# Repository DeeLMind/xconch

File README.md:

# 神奇海螺

***

## 简介

是时候该结束开发板裸奔的时代了。采用堆叠设计，拥有漂亮外观及超强扩展性。一款完全开源的结构及通用硬件扩展平台，旨在大家能更欢乐的DIY。

项目首页：https://github.com/xboot/xconch

## 名称的由来

神奇海螺，源自网友`word天`lymz@foxmail.com(QQ928882442)的网名，只因在激烈的项目取名讨论中，一张惊天图片，高逼格的意境，贴合式奶骑，迅速定论，结束了`一个完全开源的，未知项目名称的，有着炫酷外观及超强堆叠扩展性的装逼DIY套件`混沌态描述。

在这里同样感谢如下网友参与头脑风暴，积极献计献策。排名不分先后，如有遗漏还请海涵：

| 网名         | QQ         |
| ---------- | ---------- |
| 非飞         | 6278495    |
| 挖坑侠晕哥      | 516333132  |
| 迪卡魏曼依奇君    | 932668000  |
| Val劲       | 2452013147 |
| Bumbee     | 1059270763 |
| 忽忽         | 12931577   |
| Dictionary | 179670618  |
| 怪盗Kid      | 783837037  |
| 暗╰☆╮夜      | 2819617028 |
| 已完成。 成。 成。 | 2495841298 |
| flame      | 470230832  |
| Robe       | 82796620   |
| 橘子         | 2535418266 |
| 肠子         | 553010120  |
| 〃阿慕慕ぐ      | 819876772  |
| 郑          | 158754845  |
| Mpax       | 530465617  |
| K.o.s      | 13712417   |
| ——         | 673576000  |
| Jarvis     | 390246362  |
| Fourier    | 157871537  |
| 和自己赛跑™®    | 254762059  |
| 冰水寒        | 76884682   |
| 我在做梦       | 345340585  |
| 宁以远        | 800636     |
| 火龙果Geek    | 1136632326 |

## [神奇海螺LOGO](https://raw.githubusercontent.com/xboot/xconch/master/documents/images/logo.svg)

## 项目意义及最终目标

神奇海螺项目旨在解决现在市面上无数大大小小的开发板不仅互不兼容，而且绝大部分都还没有外壳，这对于DIY来说，实在不太友好。辛辛苦苦开发了某款功能，却只见到眼前如蜘蛛网般的各种导线，实在没了心情，你说你开发的这个功能有多先进，有多强大，在面对眼前如此景象时，我想您也少了份底气，神奇海螺要做的，就是让您能自豪的说，我开发的这个功能随时可以以产品级的形态来演示。

神奇海螺最终目标不是做各种开发板或开发平台，而是定义一套完整的标准技术规范，包括各种机械结构及电气信号。当然在神奇海螺项目中也会实现一些有典型意义的开发平台，旨在提供标准参考实现。同时，这也是一个持续性的过程，尽可能丰富基于神奇海螺标准的各种开发平台及扩展模块。

## 神奇海螺授权模式

神奇海螺采用免授权模式，官方不保留任何权利，任何组织及个人可无偿使用神奇海螺的各种成果，包括各种商业用途。神奇海螺LOGO，外观，技术规范，具体平台实现，官方都不保留任何权利，想用就用，想拿就拿，想卖就卖，如果硬是要给这种授权模式定义一个概念的话，那就叫做`阳光授权`吧。`阳光授权`是自保护的，禁止任何组织及个人持有版权、商标、专利等一系列破坏神奇海螺`阳光授权`模式的行为。一旦发生，该组织及个人将不再拥有`阳光授权`所赋予的任何权利，同时该破坏行为自动失效。阳光不属于任何一个人，阳光属于每一个人。

## 如何加入组织及贡献自己的一份力量

神奇海螺整个项目寄存在`github`网站，任何想加入的组织及个人可直接`fork`项目，然后`pull request`即可。欢迎各种组织及个人踊跃贡献，官方会维护一份贡献名单，任何做出贡献的组织及个人不论贡献大小，统统记录在案，并在项目显目位置展示。

## 神奇海螺项目贡献名单，定期更新

| 网名         | QQ         |
| ---------- | ---------- |
| XBOOT         | 8192542    |
| Mpax | 530465617 |

## 结构总体设计

结构设计采用上下堆叠方式，层间既可通过磁吸连接，也可通过长螺杆，贯穿所有模块来永久固定。结构上主要有两种形态，一种是主控盒，带有各种非标准扩展接口的，包括`显示屏`，`触摸屏`，`USB OTG`，`HDMI`，`按键`等等，另一种是扩展盒，采用板对板连接器，层高`8mm`，实现无限堆叠。

### 主控盒设计

TBD

### 扩展盒设计

扩展盒边框`2mm`厚度，倒圆角，内有4颗`3mmx8mm`磁铁固定位，磁铁安装方向为正面北极，背面南极，底部堆叠接口开窗，面壳无盖，PCB板直接裸露。内部四周有6颗PCB板定位孔，依PCB板型可使用4颗或6颗自攻螺丝来固定，固定螺丝为`304十字圆头带垫自攻螺丝PWA1.7X5X4.5`。

- 3x8mm强磁：

- 304十字圆头带垫自攻螺丝PWA1.7X5X4.5

## 硬件总体设计

### 主控盒设计

任何一个具体的硬件平台，一定包含主控盒及通用扩展盒或专用扩展盒。任何一种堆叠方式中仅能有一个主控盒，并置于堆叠的最上方，通用扩展盒或专用扩展盒可以无限向下堆叠。主控盒上默认集成了各种非标准扩展功能，包括`显示屏`，`触摸屏`，`USB OTG`，`DEBUG UART`，`HDMI`，`按键`，`音频`等等，主控盒默认集成哪些功能，依据具体芯片的资源特点进行设计，尽可能提供出主控盒结构所扩展的各种功能接口，如果不存在某些功能，则需要将相对应的功能接口作留空处理。

### 扩展盒设计

扩展盒分通用扩展盒及专用扩展盒，通用扩展盒要求强制兼容，保证通用性。专用扩展盒依赖具体的主控盒，不保证兼容性。扩展盒板厚1.6mm，4个螺丝孔位或者6个螺丝孔位固定，正面限高1.8mm，背面限高2.6mm，器件尽可能放在背面，正面通过各种丝印尽可能清晰准确的描述该扩展盒，尽可能在不查阅文档时，了解该扩展盒的使用方法。

扩展盒有两种PCB板型，一种迷你板型，还有一种完整板型，两者在结构上时完全兼容的。因为整个堆叠扩展盒尺寸相对较大，而很多扩展功能相对单一，功能简单，所占PCB面积较小，为了有效降低成本，可用迷你板型来设计，迷你板型采用4颗螺丝固定，完整板型采用6颗螺丝固定，两种固定方式，都能有效保护堆叠扩展口。

- 扩展盒迷你板型尺寸如下:

- 扩展盒完整板型尺寸如下：

## 板对板连接器

板对板连接器，采用1.27间距，双排80PIN贴片排针及排母，正面采用排针，背面为排母，详细规格如下：

### 堆叠扩展口描述

堆叠扩展口采用板对板连接器，正面为排针，背面为排母，需布局在PCB的堆叠扩展位，以实现上下无限堆叠扩展。80PIN管脚，分为两个区域，一个50PIN的强制兼容区，另一个30PIN的非兼容扩展区，这样的设计既保证了堆叠的兼容性，又增强了扩展的灵活性。这也就意味着，如果需要设计一款通用扩展盒，就必须通过50PIN强制兼容区来扩展，反过来说，只要能称之为通用扩展盒的就一定是任何平台兼容的，如果一个CPU有很多特别的功能管脚需要引出，而这些信号并不在50PIN通用扩展区，这就必须通过30PIN扩展区来扩展了，扩展区不要求兼容，依据主控CPU自身的资源特点自行设计，当然基于30PIN扩展区扩展出来就是专用扩展盒了，专用扩展盒只能用于特定平台，不具有任何兼容性。通用扩展盒只能使用50PIN强制兼容区，另30PIN非兼容扩展区管脚必须需做悬空处理，专用扩展盒可以使用所有的80PIN扩展管脚。

### 强制兼容区50PIN信号定义

| 管脚 | 名字     | 管脚 | 名字      |
| :--- | -------- | ---- | --------- |
| 1    | BAT+     | 2    | BAT+      |
| 3    | VCC_5V   | 4    | VCC_5V    |
| 5    | VCC_3V3  | 6    | VCC_3V3   |
| 7    | VCC_1V8  | 8    | VCC_1V8   |
| 9    | VCC_IO   | 10   | VCC_IO    |
| 11   | GND      | 12   | GND       |
| 13   | UART_TX  | 14   | UART_RX   |
| 15   | I2C_SDA  | 16   | I2C_SCL   |
| 17   | SPI_MOSI | 18   | SPI_CLK   |
| 19   | SPI_MISO | 20   | SPI_CS    |
| 21   | SDIO_D0  | 22   | SDIO_D1   |
| 23   | SDIO_D2  | 24   | SDIO_D3   |
| 25   | SDIO_CMD | 26   | SDIO_CLK  |
| 27   | I2S_DI   | 28   | I2S_LRCLK |
| 29   | I2S_DO   | 30   | I2S_CLK   |
| 31   | CAN_H    | 32   | CAN_L     |
| 33   | USB_D+   | 34   | USB_D-    |
| 35   | PWM0     | 36   | PWM1      |
| 37   | ADC0     | 38   | ADC1      |
| 39   | DAC0     | 40   | DAC1      |
| 41   | GPIO0    | 42   | GPIO1     |
| 43   | GPIO2    | 44   | GPIO3     |
| 45   | GPIO4    | 46   | GPIO5     |
| 47   | GPIO6    | 48   | GPIO7     |
| 49   | GPIO8    | 50   | GPIO9     |

### 非兼容扩展区30PIN信号定义
| 管脚 | 名字 | 管脚 | 名字 |
| ---- | ---- | ---- | ---- |
| 51   | N/A  | 52   | N/A  |
| 53   | N/A  | 54   | N/A  |
| 55   | N/A  | 56   | N/A  |
| 57   | N/A  | 58   | N/A  |
| 59   | N/A  | 60   | N/A  |
| 61   | N/A  | 52   | N/A  |
| 63   | N/A  | 54   | N/A  |
| 65   | N/A  | 56   | N/A  |
| 67   | N/A  | 58   | N/A  |
| 69   | N/A  | 60   | N/A  |
| 71   | N/A  | 62   | N/A  |
| 73   | N/A  | 64   | N/A  |
| 75   | N/A  | 66   | N/A  |
| 77   | N/A  | 68   | N/A  |
| 79   | N/A  | 80   | N/A  |

## 结构详细设计

### 通用扩展盒

- Fusion 360结构源文件：https://github.com/xboot/xconch/blob/master/shell/xconch-extended-box.f3d

- 3D打印STL格式输出文件：https://github.com/xboot/xconch/blob/master/shell/stl/xconch-extended-box.stl

## 硬件详细设计

### 基础排针扩展盒

- 工程目录: https://github.com/xboot/xconch/tree/master/ebox-basic
- 原理图：https://github.com/xboot/xconch/blob/master/ebox-basic/ebox-basic.pdf
- PCB文件：https://github.com/xboot/xconch/blob/master/ebox-basic/ebox-basic.kicad_pcb

### 高级排针扩展盒

- 工程目录: https://github.com/xboot/xconch/tree/master/ebox-advanced
- 原理图：https://github.com/xboot/xconch/blob/master/ebox-basic/ebox-advanced.pdf
- PCB文件：https://github.com/xboot/xconch/blob/master/ebox-basic/ebox-advanced.kicad_pcb

### I2C EEPROM非易失性存储器扩展盒

- 工程目录: https://github.com/xboot/xconch/tree/master/ebox-i2c-eeprom
- 原理图：https://github.com/xboot/xconch/blob/master/ebox-i2c-eeprom/ebox-i2c-eeprom.pdf
- PCB文件：https://github.com/xboot/xconch/blob/master/ebox-i2c-eeprom/ebox-i2c-eeprom.kicad_pcb

### GPIO LED扩展盒

- 工程目录: https://github.com/xboot/xconch/tree/master/ebox-gpio-led
- 原理图：https://github.com/xboot/xconch/blob/master/ebox-gpio-led/ebox-gpio-led.pdf
- PCB文件：https://github.com/xboot/xconch/blob/master/ebox-gpio-led/ebox-gpio-led.kicad_pcb

## 讨论组，大佬聚集，请踊跃加入
神奇海螺QQ群：[658250248](https://jq.qq.com/?_wv=1027&k=5BOkXYO) (2000人)

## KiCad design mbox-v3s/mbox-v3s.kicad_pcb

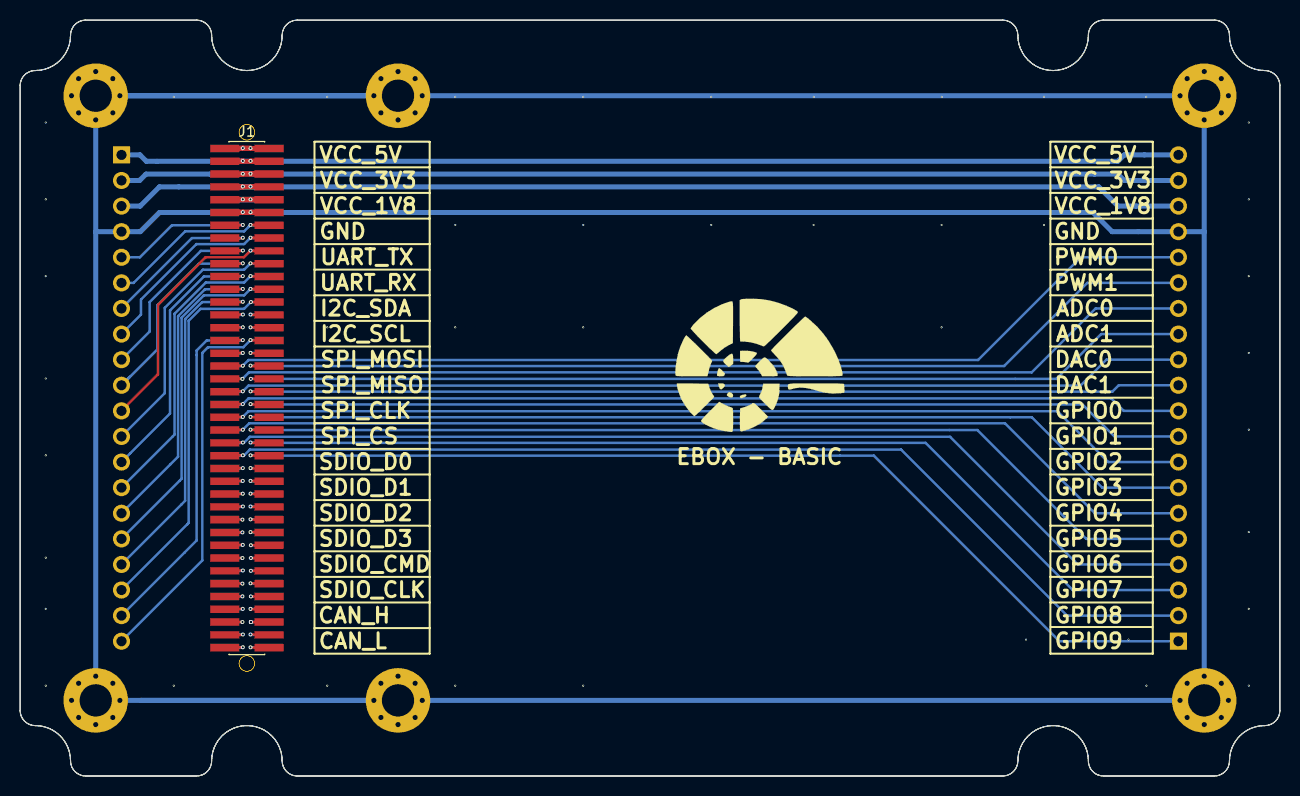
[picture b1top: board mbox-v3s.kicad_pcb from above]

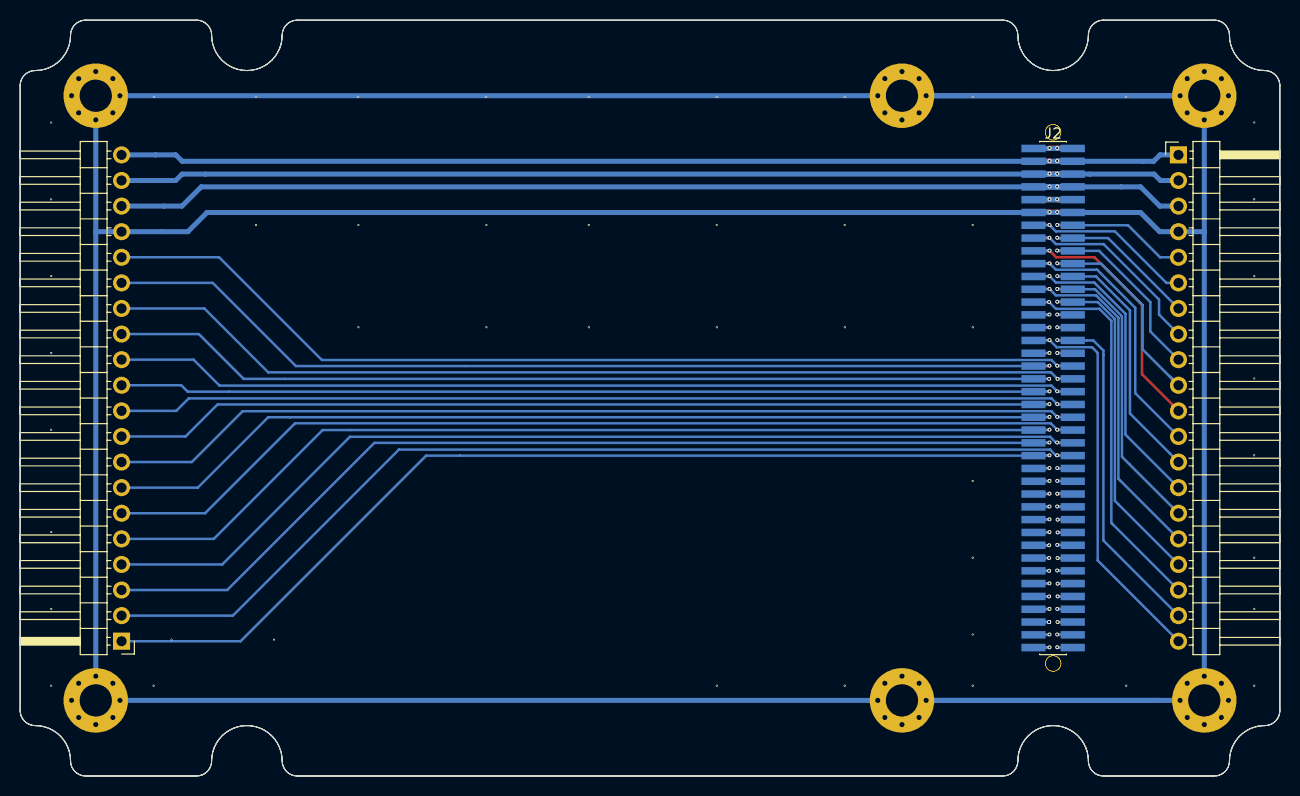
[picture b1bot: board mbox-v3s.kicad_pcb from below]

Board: 2 copper layers, 125.0 x 75.0 mm, 10 parts (3 on the bottom side), 74 nets.

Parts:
J1: xconch_pinheader_2x40
J2: xconch_pinsocket_2x40
J3, J4: Conn_01x20; PinHeader_1x20_P2.54mm_Horizontal
MK1, MK2, MK3, MK4, MK5, MK6: Mounting_Hole_PAD; MountingHole_3.2mm_M3_Pad_Via

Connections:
/ADC0: J1.37, J2.38, J4.14
/ADC1: J1.38, J2.37, J4.13
/BAT+: J1.1, J1.2, J2.1, J2.2
/CAH_H: J1.31, J2.32, J3.19
/CAN_L: J1.32, J2.31, J3.20
/DAC0: J1.39, J2.40, J4.12
/DAC1: J1.40, J2.39, J4.11
/GPIO0: J1.41, J2.42, J4.10
/GPIO1: J1.42, J2.41, J4.9
/GPIO2: J1.43, J2.44, J4.8
/GPIO3: J1.44, J2.43, J4.7
/GPIO4: J1.45, J2.46, J4.6
/GPIO5: J1.46, J2.45, J4.5
/GPIO6: J1.47, J2.48, J4.4
/GPIO7: J1.48, J2.47, J4.3
/GPIO8: J1.49, J2.50, J4.2
/GPIO9: J1.50, J2.49, J4.1
/I2C_SCL: J1.16, J2.15, J3.8
/I2C_SDA: J1.15, J2.16, J3.7
/I2S_CLK: J1.30, J2.29
/I2S_D0: J1.29, J2.30
/I2S_DI: J1.27, J2.28
/I2S_LRCLK: J1.28, J2.27
/NC0: J1.51, J2.52
/NC1: J1.52, J2.51
/NC2: J1.53, J2.54
/NC3: J1.54, J2.53
/NC4: J1.55, J2.56
/NC5: J1.56, J2.55
/NC6: J1.57, J2.58
/NC7: J1.58, J2.57
/NC8: J1.59, J2.60
/NC9: J1.60, J2.59
/NC10: J1.61, J2.62
/NC11: J1.62, J2.61
/NC12: J1.63, J2.64
/NC13: J1.64, J2.63
/NC14: J1.65, J2.66
/NC15: J1.66, J2.65
/NC16: J1.67, J2.68
/NC17: J1.68, J2.67
/NC18: J1.69, J2.70
/NC19: J1.70, J2.69
/NC20: J1.71, J2.72
/NC21: J1.72, J2.71
/NC22: J1.73, J2.74
/NC23: J1.74, J2.73
/NC24: J1.75, J2.76
/NC25: J1.76, J2.75
/NC26: J1.77, J2.78
/NC27: J1.78, J2.77
/NC28: J1.79, J2.80
/NC29: J1.80, J2.79
/PWM0: J1.35, J2.36, J4.16
/PWM1: J1.36, J2.35, J4.15
/SDIO_CLK: J1.26, J2.25, J3.18
/SDIO_CMD: J1.25, J2.26, J3.17
/SDIO_D0: J1.21, J2.22, J3.13
/SDIO_D1: J1.22, J2.21, J3.14
/SDIO_D2: J1.23, J2.24, J3.15
/SDIO_D3: J1.24, J2.23, J3.16
/SPI_CLK: J1.18, J2.17, J3.11
/SPI_CS: J1.20, J2.19, J3.12
/SPI_MISO: J1.19, J2.20, J3.10
/SPI_MOSI: J1.17, J2.18, J3.9
/UART_RX: J1.14, J2.13, J3.6
/UART_TX: J1.13, J2.14, J3.5
/USB_D+: J1.33, J2.34
/USB_D-: J1.34, J2.33
/VCC_1V8: J1.7, J1.8, J2.7, J2.8, J3.3, J4.18
/VCC_3V3: J1.5, J1.6, J2.5, J2.6, J3.2, J4.19
/VCC_5V: J1.3, J1.4, J2.3, J2.4, J3.1, J4.20
/VCC_IO: J1.9, J1.10, J2.9, J2.10
GND: J1.11, J1.12, J2.11, J2.12, J3.4, J4.17, MK1.1, MK2.1, MK3.1, MK4.1, MK5.1, MK6.1

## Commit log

2018-02-26 add shell directory
2018-02-26 add some examples
2018-03-05 [documents]update some documents
2018-03-07 update documents
2018-03-10 add some documents files
2018-03-10 add some documents
2018-03-10 add some links
2018-03-10 update some documents
2018-03-12 add xconch-kicad-library
2018-03-12 add some kicad examples
2018-03-13 update some f3d
2018-03-15 [documents]change some pin define
2018-03-15 [ebox]modify .gitignore
2018-03-15 ebox, modify some lib
2018-03-15 add i2c eerprom
2018-03-16 [ebox]add ebox-i2c eeprom
2018-03-16 working on ebox i2c eeprom
2018-03-18 add ebox gpio led
2018-03-21 add some logo
2018-03-21 update ebox
2018-03-21 update xconch kicad library
2018-03-21 update shell
2018-03-21 add logo.f3d
2018-03-22 add new logo
2018-03-22 update logo
2018-03-22 add logo for f3d
2018-03-23 add led extended box
2018-03-26 add logo for some pcb
2018-03-26 remove logo.f3d
2018-03-27 add basic ebox
2018-03-29 add advanced ebox
2018-03-29 add xconch-extended-box-pinheader
2018-03-29 remove some step
2018-03-30 add mbox v3s
2018-03-30 add ebox dxf files
